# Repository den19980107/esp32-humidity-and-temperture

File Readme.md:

# ESP32 Environmental Monitor

A comprehensive IoT project for environmental monitoring with Home Assistant integration, featuring an event-driven architecture and web-based configuration interface.

## 🌟 Features

### Core Functionality
1. **Environmental Monitoring**: DHT11 sensor for temperature and humidity detection
2. **Smart Night Light**: Automatic LED control based on ambient light levels with photoresistor
3. **OLED Display**: Real-time sensor data visualization with status indicators
4. **Cloud Integration**: MQTT-based data upload with Home Assistant auto-discovery
5. **Remote Control**: LED control via Home Assistant or MQTT commands
6. **Web Configuration**: User-friendly WiFi setup interface with network scanning

### Advanced Features
- **Automatic Fallback**: Access Point mode when WiFi credentials are not configured
- **Persistent Configuration**: SPIFFS-based storage for WiFi and device settings  
- **Event-Driven Architecture**: Modular design with EventBus pattern
- **Hardware Abstraction**: Clean interfaces for sensors, display, and connectivity
- **Real-time Monitoring**: Web-based status dashboard with live updates
- **Error Handling**: Comprehensive logging and graceful error recovery

## 🎥 Demo

https://www.youtube.com/shorts/sdgEsP3yd80

## 🔧 Hardware

### Project Photos

**Front View:**

**Back View:**

### Component List
- **ESP32 Development Board** (ESP32-DOIT-DEVKIT-V1)
- **DHT11** - Temperature and humidity sensor
- **SSD1306 OLED Display** - 128x64 I2C display
- **Photoresistor** - Light intensity detection
- **LED** - Night light and status indicator
- **Resistors** - Pull-up and current limiting

### Pin Configuration
```cpp
// Sensor Pins
DHT11_PIN = 13        // Temperature/Humidity sensor
PHOTORESISTOR_PIN = 39 // Light sensor (analog)
LED_PIN = 25          // Night light LED

// I2C Display
SDA_PIN = 32          // I2C Data
SCL_PIN = 33          // I2C Clock
```

### Schematic Diagram

### PCB Layout

## 💾 Software Architecture

### Event-Driven Design
The system is built using a modern event-driven architecture replacing the original state machine approach:

```
┌─────────────────┐    ┌─────────────────┐    ┌─────────────────┐
│   Sensor Layer  │    │  Hardware Layer │    │    Core App     │
│                 │    │                 │    │                 │
│ • DHTSensor     │───▶│ • WiFiManager   │───▶│ • EventBus      │
│ • Photoresistor │    │ • MQTTClient    │    │ • Config        │
│                 │    │ • LEDController │    │ • Logger        │
└─────────────────┘    └─────────────────┘    └─────────────────┘
                                │                       │
┌─────────────────┐             │              ┌─────────────────┐
│ Display Layer   │             │              │   Web Server    │
│                 │             │              │                 │
│ • OLEDDisplay   │◀────────────┼──────────────│ • Status Page   │
│ • Status Info   │             │              │ • WiFi Config   │
│                 │             │              │ • Network Scan  │
└─────────────────┘             ▼              └─────────────────┘
                    ┌─────────────────┐
                    │ Home Assistant  │
                    │                 │
                    │ • Auto Discovery│
                    │ • MQTT Topics   │
                    │ • LED Control   │
                    └─────────────────┘
```

### Key Components

#### Core Classes
- **`App`**: Main application orchestrator with event handling
- **`EventBus`**: Publish/subscribe system for component communication
- **`Config`**: Configuration management with SPIFFS persistence

#### Hardware Abstractions
- **`ISensorReader`**: Interface for sensor data reading
- **`IDisplayDriver`**: Interface for display operations  
- **`ILedController`**: Interface for LED control
- **`WiFiManager`**: WiFi connection and Access Point management
- **`MQTTClient`**: MQTT communication with Home Assistant integration

## 🚀 Getting Started

### Prerequisites
- **PlatformIO CLI** - Development environment
- **ESP32 Development Board** - Target hardware
- **USB Cable** - For programming and power

### Installation

1. **Clone the repository**
   ```bash
   git clone <repository-url>
   cd "esp32 humidity and temperture"
   ```

2. **Install dependencies**
   ```bash
   pio run -t compiledb
   ```

3. **Build and upload**
   ```bash
   pio run -e upesy_wroom -t upload
   ```

4. **Monitor serial output**
   ```bash
   pio monitor -e upesy_wroom
   ```

### Initial Setup

1. **Power on the ESP32** - It will start in Access Point mode
2. **Connect to WiFi** - Look for "ESP32-Config-36EC" network  
3. **Open configuration page** - Navigate to http://192.168.4.1
4. **Configure WiFi** - Select your network and enter password
5. **Automatic restart** - ESP32 will connect to your WiFi network
6. **Access status page** - Monitor at the assigned IP address

## 📱 Web Interface

### WiFi Configuration

**Features:**
- Network scanning and selection
- Manual SSID entry support
- Password input with validation
- Automatic restart after configuration
- Responsive design for mobile devices

### Status Dashboard
- Real-time sensor readings
- WiFi connection status
- MQTT connection health
- System information (uptime, memory)
- LED control status
- Home Assistant integration status

## 🏠 Home Assistant Integration

### Automatic Discovery
The device automatically registers with Home Assistant using MQTT Discovery:

```yaml
# Automatically created entities:
sensor.esp32_temperature
sensor.esp32_humidity  
sensor.esp32_light_level
sensor.esp32_memory_free
sensor.esp32_memory_total
light.esp32_led
```

### MQTT Topics
```
# Data Publishing
Advantech/24dcc3a736ec/data

# LED Control  
Advantech/24dcc3a736ec/led

# Discovery Topics
homeassistant/sensor/24dcc3a736ec/temperature/config
homeassistant/sensor/24dcc3a736ec/humidity/config
homeassistant/light/24dcc3a736ec/led/config
```

## ⚙ Configuration

### Default Settings
```json
{
  "wifi": {
    "ssid": "",
    "password": ""
  },
  "mqtt": {
    "broker": "192.168.31.21",
    "port": 1883,
    "username": "user",
    "password": "passwd",
    "edgeId": "24dcc3a736ec"
  },
  "sensor": {
    "dhtPin": 13,
    "photoresisterPin": 39,
    "ledPin": 25,
    "photoresisterThreshold": 800,
    "uploadFrequency": 5000,
    "nightLightDuration": 600000
  }
}
```

### Customization
- Modify `src/core/config.cpp` for default values
- Use web interface for WiFi configuration
- MQTT settings configurable via code (future: web interface)

## 🔧 Development

### Project Structure
```
src/
├── core/
│   ├── app.cpp              # Main application logic
│   ├── config.cpp           # Configuration management
│   ├── event_bus.cpp        # Event system
│   ├── interfaces.h         # Hardware abstractions
│   └── logger.cpp           # Logging system
├── hardware/
│   ├── dht_sensor.cpp       # DHT11 sensor driver
│   ├── oled_display.cpp     # SSD1306 display driver
│   ├── led_controller.cpp   # LED control
│   ├── wifi_manager.h       # WiFi management
│   └── mqtt_client.h        # MQTT communication
└── main.cpp                 # Entry point
```

### Build Commands
```bash
# Build only
pio run -e upesy_wroom

# Upload to device  
pio run -e upesy_wroom -t upload

# Monitor serial output
pio monitor -e upesy_wroom

# Clean build
pio run -e upesy_wroom -t clean

# Erase flash (reset WiFi config)
pio run -e upesy_wroom -t erase
```

## 🐛 Troubleshooting

### WiFi Issues
- **Can't find ESP32 network**: Wait 30 seconds after power-on for AP mode
- **Configuration not saving**: Check serial logs for SPIFFS errors
- **Won't connect to WiFi**: Verify password and network availability

### MQTT Issues  
- **Not connecting**: Check broker IP and credentials in config
- **Home Assistant not discovering**: Verify MQTT broker is running
- **LED control not working**: Check MQTT topic subscription

### Hardware Issues
- **No sensor readings**: Check DHT11 wiring and pin configuration
- **Display not working**: Verify I2C connections (SDA/SCL pins)
- **LED not responding**: Check LED pin and current limiting resistor

## 📈 Future Enhancements

- [ ] Web-based MQTT configuration
- [ ] OTA (Over-The-Air) firmware updates
- [ ] Additional sensor support (BME280, etc.)
- [ ] Data logging to SD card
- [ ] Battery power optimization
- [ ] Custom dashboard themes
- [ ] Multi-language support

## 📄 License

This project is open source and available under the MIT License.

## 🤝 Contributing

Contributions are welcome! Please feel free to submit pull requests or open issues for bugs and feature requests.

---

*This project serves as a comprehensive example of modern ESP32 development with clean architecture, web interfaces, and IoT integration.*

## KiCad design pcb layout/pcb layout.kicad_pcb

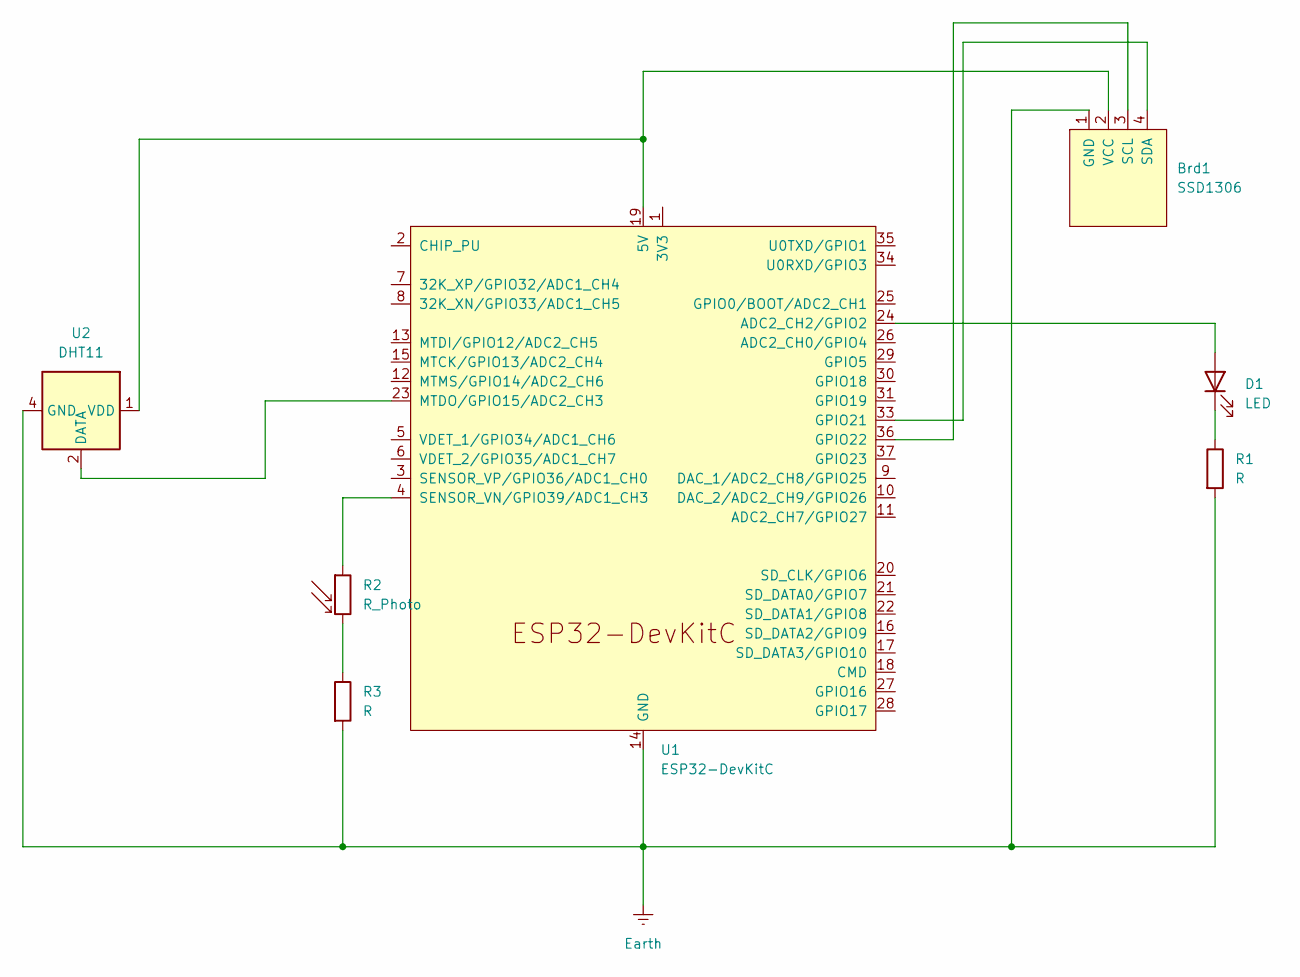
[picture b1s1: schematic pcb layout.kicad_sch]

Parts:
Brd1: SSD1306; 128x64OLED
D1: LED; LED_D3.0mm_Horizontal_O6.35mm_Z10.0mm
R1: R; R_Axial_DIN0204_L3.6mm_D1.6mm_P7.62mm_Horizontal
R2: R_Photo; Osram_DIL2_4.3x4.65mm_P5.08mm
R3: R; R_Axial_DIN0204_L3.6mm_D1.6mm_P5.08mm_Horizontal
U1: ESP32-DevKitC
U2: DHT11; Aosong_DHT11_5.5x12.0_P2.54mm

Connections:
Earth: Brd1.1 (GND), R1.2, R3.2, U1.14 (GND), U1.32 (GND), U1.38 (GND), U2.4 (GND)
unnamed: Brd1.3 (SCL), U1.36 (GPIO22)
unnamed: Brd1.4 (SDA), U1.33 (GPIO21)
unnamed: Brd1.2 (VCC), U1.19 (5V), U2.1 (VDD)
unnamed: D1.2 (A), U1.24 (ADC2_CH2/GPIO2)
unnamed: D1.1 (K), R1.1
unnamed: R2.2, R3.1
unnamed: U1.23 (MTDO/GPIO15/ADC2_CH3), U2.2 (DATA)
unnamed: R2.1, U1.4 (SENSOR_VN/GPIO39/ADC1_CH3)

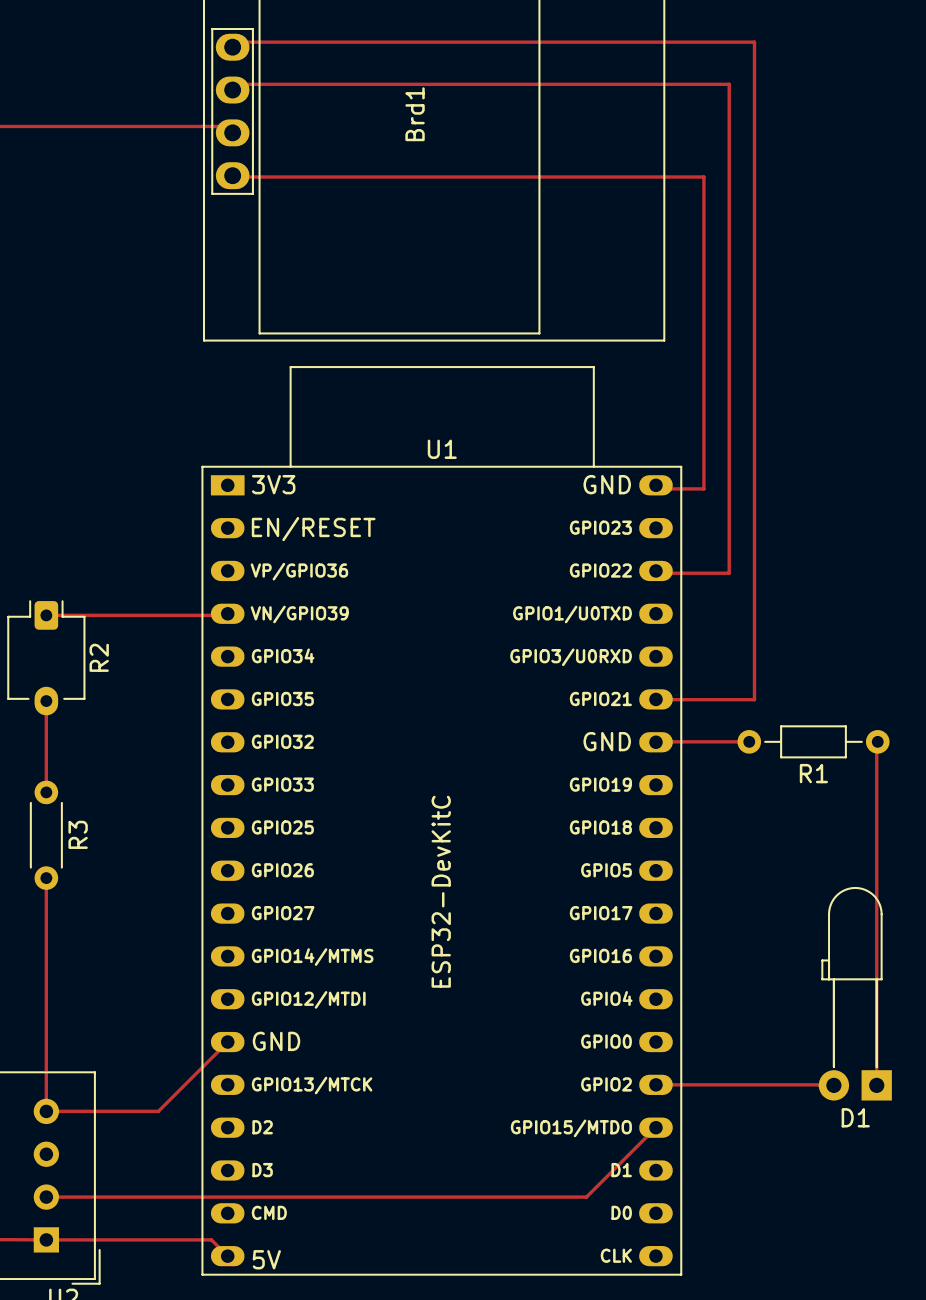
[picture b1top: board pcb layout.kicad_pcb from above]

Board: 2 copper layers, 7 parts (0 on the bottom side), 9 nets.

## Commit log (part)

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2024-05-25 refactor: seperate different function to seperate file
2024-05-26 feat: support wifi and mqtt
2024-05-26 update string declare
2024-06-05 feat: update pcb
2024-06-05 refactor: change to using state machine to implement app logic
2024-06-05 feat: add makefile
2024-06-05 feat: add clang-format
2024-06-05 feat: add readme
2024-06-06 feat: let led status display in the center of screen
2024-06-06 fix: typo
2024-06-07 feat: support run server for user to fill up wifi info and connect
2024-06-07 feat: update readme
2024-06-07 feat: move the html to the seperate file
2024-06-07 feat: support fill up the device config in ui
2024-06-13 feat: upadte readme for demo video
2024-06-25 fix: update
2024-06-27 feat: support homeassistant discovery
2024-06-29 feat: support home assistant
2024-06-29 refactor: clean up code
2024-06-29 fix: should compare with user setting edge id
2024-06-30 fix: after connect to wifi, stop ap mode, and add device class to each sensor
2024-07-01 fix: only need to disconnect ap, no need to disconnect wifi
2024-10-21 feat: support light sleep mode to reduce power usage
2025-03-29 fix: memory leak
2025-03-29 feat: add the current memory to the sensor data
2025-03-30 feat: support reconnect to wifi
2025-04-07 fix: memory leak when reconnect wifi
2025-05-04 fix: update the monitor when photoresister value change too
2025-05-04 fix: change to use gpio 32 and 33 as I2C pin
2025-05-04 fix: update the monitor to show the bigger text and the light level as a bar
2025-05-04 fix: update header file
2025-05-04 fix: update define
2025-06-28 fix: remove sleep
2025-07-20 fix: led won't turn off after 10 min
2025-07-20 feat: add led countdown in the top right of ssd1306
